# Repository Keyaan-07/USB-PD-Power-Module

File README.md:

# USB-PD-Power-Supply
Sometimes it happens that when playing with electronics, we need more than 5V or 9V. USB PD Power Supply Solves this issue.  
By using USB PD Protocol, it can negotiate more than 5V from the USB PD charger. It can give voltage outputs as supported by the PD charger from 5V to 20V and it also supports the new USB PPS protocol which allows us set the voltage according to our own needs. For Example, if some device needs 18V, PPS can do the task and it could supply voltage.  

USB PD Power Supply can use both PD and PPS to cupply voltage. The microcontroller is the OG RP2040, which communications with the AP33772SDKZ USB PD negotiator IC to negotiate voltage levels. The Voltage and max current settings are controllable using the two rotary encoders present on the PCB.  

## How the heck do you assemble this thing?
First of all, you start with the gerber and upload it to your desired pcb manufacturer, I am gonna use [PCB Power](https://pcbpower.com). Now you order the PCB and all the components, and you wait, after they arrive, you cook(assemble) the PCB. Then what you do is that you upload the code and start using, 3D printed case is optional but you could download the files for that too! Flash firmware(firmware to come in a few days) on RP2040 using thonny or other software and boom your [USB-PD-Power-supply](https://github.com/Keyaan-07/USB-PD-Power-Supply/) is ready

## Why I chose to make this Project
I chose to make this project mainly because of the power issues i face. A few days ago, I wanted to power a coil for an electromagnet, i was not able to power it because of power supply from the Power bank (5V) was not enough, so i had the idea of making this because my dad's phone has a USB PD Charger so i could use that charger to power electronics that require higher voltage. That type of a project would be too simple, so i also added two rotary encoders and make a dedicated power supply. 

# Images

<br>

<br>  

# BOM - Bill Of All Materials:

| ITEM NAME                                              | ITEM PRICE        | FUNCTION                                                       | URL                                                                                                                                                                                                                                                                                                                                                                                           |
| ------------------------------------------------------ | ----------------- | -------------------------------------------------------------- | --------------------------------------------------------------------------------------------------------------------------------------------------------------------------------------------------------------------------------------------------------------------------------------------------------------------------------------------------------------------------------------------- |
| PCB Manufacturing(5 units)                             | $29.20            | Main PCB                                                       | [https://pcbpower.com](https://pcbpower.com/)                                                                                                                                                                                                                                                                                                                                                 |
| PCB Components                                         | $32.12            | All the PCB Components                                         | [https://lcsc.com](https://lcsc.com/)                                                                                                                                                                                                                                                                                                                                                         |
| PCB Stencil                                            | $27.25            | Stencil for Assembly of PCB                                    | [https://pcbpower.com](https://pcbpower.com/)                                                                                                                                                                                                                                                                                                                                                 |
| OLED and Headers + M3 screws and inserts, Solder Paste | $9.13             | Displays voltage and current levels, assembly body, and solder | https://roboticsdna.in/product/1-3-inch-iic-128x64-oled-display-module-4-pin-blue/ ,  https://roboticsdna.in/product/m3-x-6mm-brass-heat-set-threaded-round-insert-nut-25-pcs/ ,  https://roboticsdna.in/product/m3-6mm-ss-25-pieces/ ,  https://roboticsdna.in/product/2-54mm-1x20-right-angle-female-header-strip-2/ ,   https://roboticsdna.in/product/original-mechanic-30g-solder-paste/ |
| 3d parts                                               | $7.98             | 3d parts                                                       | [https://3ding.in/](https://3ding.in/)                                                                                                                                                                                                                                                                                                                                                        |
| Total                                                  | $105.68           |                                                                |                                                                                                                                                                                                                                                                                                                                                                                               |
### Note: There are a few resistors and capacitors, which had very high minimum order quantity(MOQ), about 100 pieces so i had to forcefully include those, which i will be utilising in my next highway projects. And tbh the prices were very less(about $0.002 per piece) so i think it is alright

# PCB Components Breakdown:  

| Id | Designator                           | MPN                  | Footprint                                      | DNP | MOQ | Price  | Quantity | Designation                        | Amount | LCSC Part No. | Supplier and ref                                                                                                                           |
| -- | ------------------------------------ | -------------------- | ---------------------------------------------- | --- | --- | ------ | -------- | ---------------------------------- | ------ | ------------- | ------------------------------------------------------------------------------------------------------------------------------------------ |
| 1  | Q1,Q2                                | BSS138               | SOT-23                                         | No  | Yes | 0.0571 | 10       | BSS138                             | 0.571  | C82045        | https://www.lcsc.com/product-detail/MOSFETs_onsemi-BSS138LT1G_C82045.html?s_z=n_bss138                                                     |
| 2  | C21,C1,C2,C22                        | GRM21BR61H106KE43L   | C_0805_2012Metric                              | No  | Yes | 0.0509 | 100      | 10u                                | 5.09   | C440198       | https://www.lcsc.com/product-detail/Multilayer-Ceramic-Capacitors-MLCC-SMD-SMT_Samsung-Electro-Mechanics-CL21A106KBYQNNE_C2932476.html     |
| 3  | R17,R10,R9,R20,R18,R19,R7,R6,R8,R11  | RC0402FR-7W5K1L      | R_0402_1005Metric                              | No  | Yes | 0.0057 | 100      | 5.1k                               | 0.57   | C278598       | https://www.lcsc.com/product-detail/Chip-Resistor-Surface-Mount_PANASONIC-ERJ2RKF5101X_C278598.html                                        |
| 4  | C14,C15                              | GJM1555C1H150FB01D   | C_0402_1005Metric                              | No  | Yes | 0.021  | 20       | 15p                                | 0.42   | C441742       | https://www.lcsc.com/product-detail/Multilayer-Ceramic-Capacitors-MLCC-SMD-SMT_Murata-Electronics-GJM1555C1H150FB01D_C441742.html          |
| 5  | J5                                   | generic              | PinHeader_1x04_P2.54mm_Vertical                | Yes | Yes | 0      | 1        | Conn_01x04_Socket_external         | 0      |               | \-                                                                                                                                         |
| 6  | R2,R1,R5,R16                         | ERJPA2F1001X         | R_0402_1005Metric                              | No  | Yes | 0.027  | 20       | 1k                                 | 0.54   | C427241       | https://www.lcsc.com/product-detail/Chip-Resistor-Surface-Mount_PANASONIC-ERJPA2F1001X_C427241.html                                        |
| 7  | Q4,Q3                                | AON7672E             | TRANS_AONR21307                                | No  | No  | 0.7665 | 5        | AON7672E                           | 3.8325 | C176755       | https://www.lcsc.com/product-detail/MOSFETs_Alpha-Omega-Semicon-AON7262E_C176755.html                                                      |
| 8  | C12,C18,C4,C8,C13,C3,C7,C9,C6,C5,C17 | GRM155R61H104JE14D   | C_0402_1005Metric                              | No  | Yes | 0.0074 | 100      | 100n                               | 0.74   | C426067       | https://www.lcsc.com/product-detail/Multilayer-Ceramic-Capacitors-MLCC-SMD-SMT_Murata-Electronics-GRM155R61H104JE14D_C426067.html          |
| 9  | J1                                   | TYPE-C16PIN          | USB_C_Receptacle_XKB_U262-16XN-4BVC11          | No  | Yes | 0.0656 | 10       | USB_C_Receptacle_USB2.0_14P_RP2040 | 0.656  | C393939       | https://www.lcsc.com/product-detail/USB-Connectors_SHOU-HAN-TYPE-C16PIN_C393939.html?s_z=n_USB_C_Receptacle_XKB_U262-16XN-4BVC11           |
| 10 | C10,C11,C16                          | GRM155R61H105KE05D   | C_0402_1005Metric                              | No  | Yes | 0.0247 | 20       | 1u                                 | 0.494  | C1518208      | https://www.lcsc.com/product-detail/Multilayer-Ceramic-Capacitors-MLCC-SMD-SMT_Murata-Electronics-GRM155R61H105KE05D_C1518208.html         |
| 11 | J4                                   | generic              | PinHeader_1x03_P2.54mm_Vertical                | Yes | Yes | 0      | 1        | Conn_01x03_Pin_SWD                 | 0      |               | \-                                                                                                                                         |
| 12 | R13                                  | RCS040210K0FKED      | R_0402_1005Metric                              | No  | Yes | 0.0278 | 50       | 10k                                | 1.39   | C3020235      | https://www.lcsc.com/product-detail/Chip-Resistor-Surface-Mount_Vishay-Intertech-RCS040210K0FKED_C3020235.html                             |
| 13 | D1,D2                                | 16-213/GHC-YR1S1N/3T | LED_0402_1005Metric                            | No  | Yes | 0.0526 | 20       | LED                                | 1.052  | C2980183      | https://www.lcsc.com/product-detail/LED-Indication-Discrete_Everlight-Elec-16-213-GHC-YR1S1N-3T_C2980183.html?s_z=n_LED                    |
| 14 | U1                                   | RP2040               | QFN-56-1EP_7x7mm_P0.4mm_EP3.2x3.2mm            | No  | No  | 1.1274 | 2        | RP2040                             | 2.2548 | C2040         | https://www.lcsc.com/product-detail/Microcontrollers-MCU-MPU-SOC_Raspberry-Pi-RP2040_C2040.html?s_z=n_rp2040                               |
| 15 | J2                                   | TYPE-C16PIN          | USB_C_Receptacle_XKB_U262-16XN-4BVC11          | No  | No  | 0.0656 | 0        | USB_C_Receptacle_USB2.0_14P        | 0      | C393939       | https://www.lcsc.com/product-detail/USB-Connectors_SHOU-HAN-TYPE-C16PIN_C393939.html?s_z=n_USB_C_Receptacle_XKB_U262-16XN-4BVC11           |
| 16 | Y1                                   | ABM8-272-T3          | Crystal_SMD_3225-4Pin_3.2x2.5mm                | No  | No  | 0.3856 | 2        | Crystal_GND24                      | 0.7712 | C20625731     | https://www.lcsc.com/product-detail/Crystals_Abracon-LLC-ABM8-272-T3_C20625731.html?s_z=n_abm8                                             |
| 17 | D3,D4                                | ESDS314DBVR          | SOT-23-5                                       | No  | Yes | 0.2348 | 5        | ESDS314DBVR                        | 1.174  | C1847859      | https://www.lcsc.com/product-detail/ESD-and-Surge-Protection-TVS-ESD_Texas-Instruments-ESDS314DBVR_C1847859.html?s_z=n_ESDS314DBVR         |
| 18 | TH1                                  | NCP15XH103F03RC      | R_0402_1005Metric                              | No  | Yes | 0.0104 | 1        | 10k @ 25C                          | 0.0104 | C209959       | https://www.lcsc.com/product-detail/NTC-Thermistors_TDK-NTCG103JF103FT1_C209959.html                                                       |
| 19 | D5                                   | 16-213/GHC-YR1S1N/3T | LED_0402_1005Metric_Pad0.77x0.64mm_HandSolder  | No  | Yes | 0.0526 | 0        | LED                                | 0      | C2980183      | https://www.lcsc.com/product-detail/LED-Indication-Discrete_Everlight-Elec-16-213-GHC-YR1S1N-3T_C2980183.html?s_z=n_LED                    |
| 20 | R14                                  | ERJPA2J100X          | R_0402_1005Metric                              | No  | Yes | 0.0201 | 20       | 10                                 | 0.402  | C427198       | https://www.lcsc.com/product-detail/Chip-Resistor-Surface-Mount_PANASONIC-ERJPA2J100X_C427198.html                                         |
| 21 | J6                                   | 6.94108E+11          | BarrelJack_Wuerth_6941xx301002                 | Yes | Yes | 0      | 0        | Barrel_Jack                        | 0      |               |                                                                                                                                            |
| 22 | SW3                                  | EC11E1820402         | RotaryEncoder_Alps_EC11E-Switch_Vertical_H20mm | No  | Yes | 1.548  | 1        | RotaryEncoder_Switch_Current       | 1.548  | C361167       | https://www.lcsc.com/product-detail/Rotary-Encoders_ALPSALPINE-EC11E1820402_C361167.html                                                   |
| 23 | R4,R3                                | ERJ2GEJ270X          | R_0402_1005Metric                              | No  | Yes | 0.0039 | 100      | 27                                 | 0.39   | C278580       | https://www.lcsc.com/product-detail/Chip-Resistor-Surface-Mount_PANASONIC-ERJ2GEJ270X_C278580.html                                         |
| 24 | IC1                                  | AP33772DKZ-13        | AP33772SDKZ13FA01                              | No  | No  | 1.6472 | 2        | AP33772SDKZ-13-FA01                | 3.2944 | C5244513      | https://www.lcsc.com/product-detail/AC-DC-Controllers-and-Regulators_Diodes-Incorporated-AP33772DKZ-13_C5244513.html?s_z=n_AP3377          |
| 25 | SW2                                  | EC11E1820402         | RotaryEncoder_Alps_EC11E-Switch_Vertical_H20mm | No  | Yes | 1.548  | 1        | RotaryEncoder_Switch_Voltage       | 1.548  | C361167       | https://www.lcsc.com/product-detail/Rotary-Encoders_ALPSALPINE-EC11E1820402_C361167.html                                                   |
| 26 | U3                                   | W25Q128JVSIM         | SOIC-8_5.23x5.23mm_P1.27mm                     | No  | Yes | 1.1083 | 5        | W25Q128JVS                         | 5.5415 | C2613930      | https://www.lcsc.com/product-detail/NOR-FLASH_Winbond-Elec-W25Q128JVSIM_C2613930.html?s_z=n_W25Q128JVS                                     |
| 27 | R12                                  | PA0402FRL570R005L    | R_0402_1005Metric                              | No  | Yes | 0.0679 | 5        | 5m                                 | 0.3395 | C723468       | https://www.lcsc.com/product-detail/Current-Sense-Resistors-Shunt-Resistors_YAGEO-PA0402FRL570R005L_C723468.html                           |
| 28 | J3                                   | generic              | PinHeader_1x04_P2.54mm_Vertical                | Yes | Yes | 0      | 0        | Conn_01x04_Socket_OLED             | 0      |               |                                                                                                                                            |
| 29 | U2                                   | AMS1117S-3.3         | SOT-89-3                                       | No  | Yes | 0.1057 | 5        | AMS1117s-3.3                       | 0.5285 | C917152       | https://www.lcsc.com/product-detail/Voltage-Regulators-Linear-Low-Drop-Out-LDO-Regulators_JSMSEMI-AMS1117S-3-3_C917152.html?s_z=n_ams1117s |
| 30 | R15                                  | ERJPA2J101X          | R_0402_1005Metric                              | No  | Yes | 0.0374 | 20       | 100                                | 0.748  | C427204       | https://www.lcsc.com/product-detail/Chip-Resistor-Surface-Mount_PANASONIC-ERJPA2J101X_C427204.html                                         |
| 31 | SW1                                  | PTS810SJK250SMTRLFS  | SW_SPST_PTS810                                 | No  | No  | 0.6744 | 2        | SW_Push                            | 1.3488 | C221896       | https://www.lcsc.com/product-detail/Tactile-Switches_C-K-PTS810SJK250SMTRLFS_C221896.html?s_z=n_C221896                                    |

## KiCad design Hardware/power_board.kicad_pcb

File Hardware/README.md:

# Hardware for USB-PD-Power-supply is in this directory

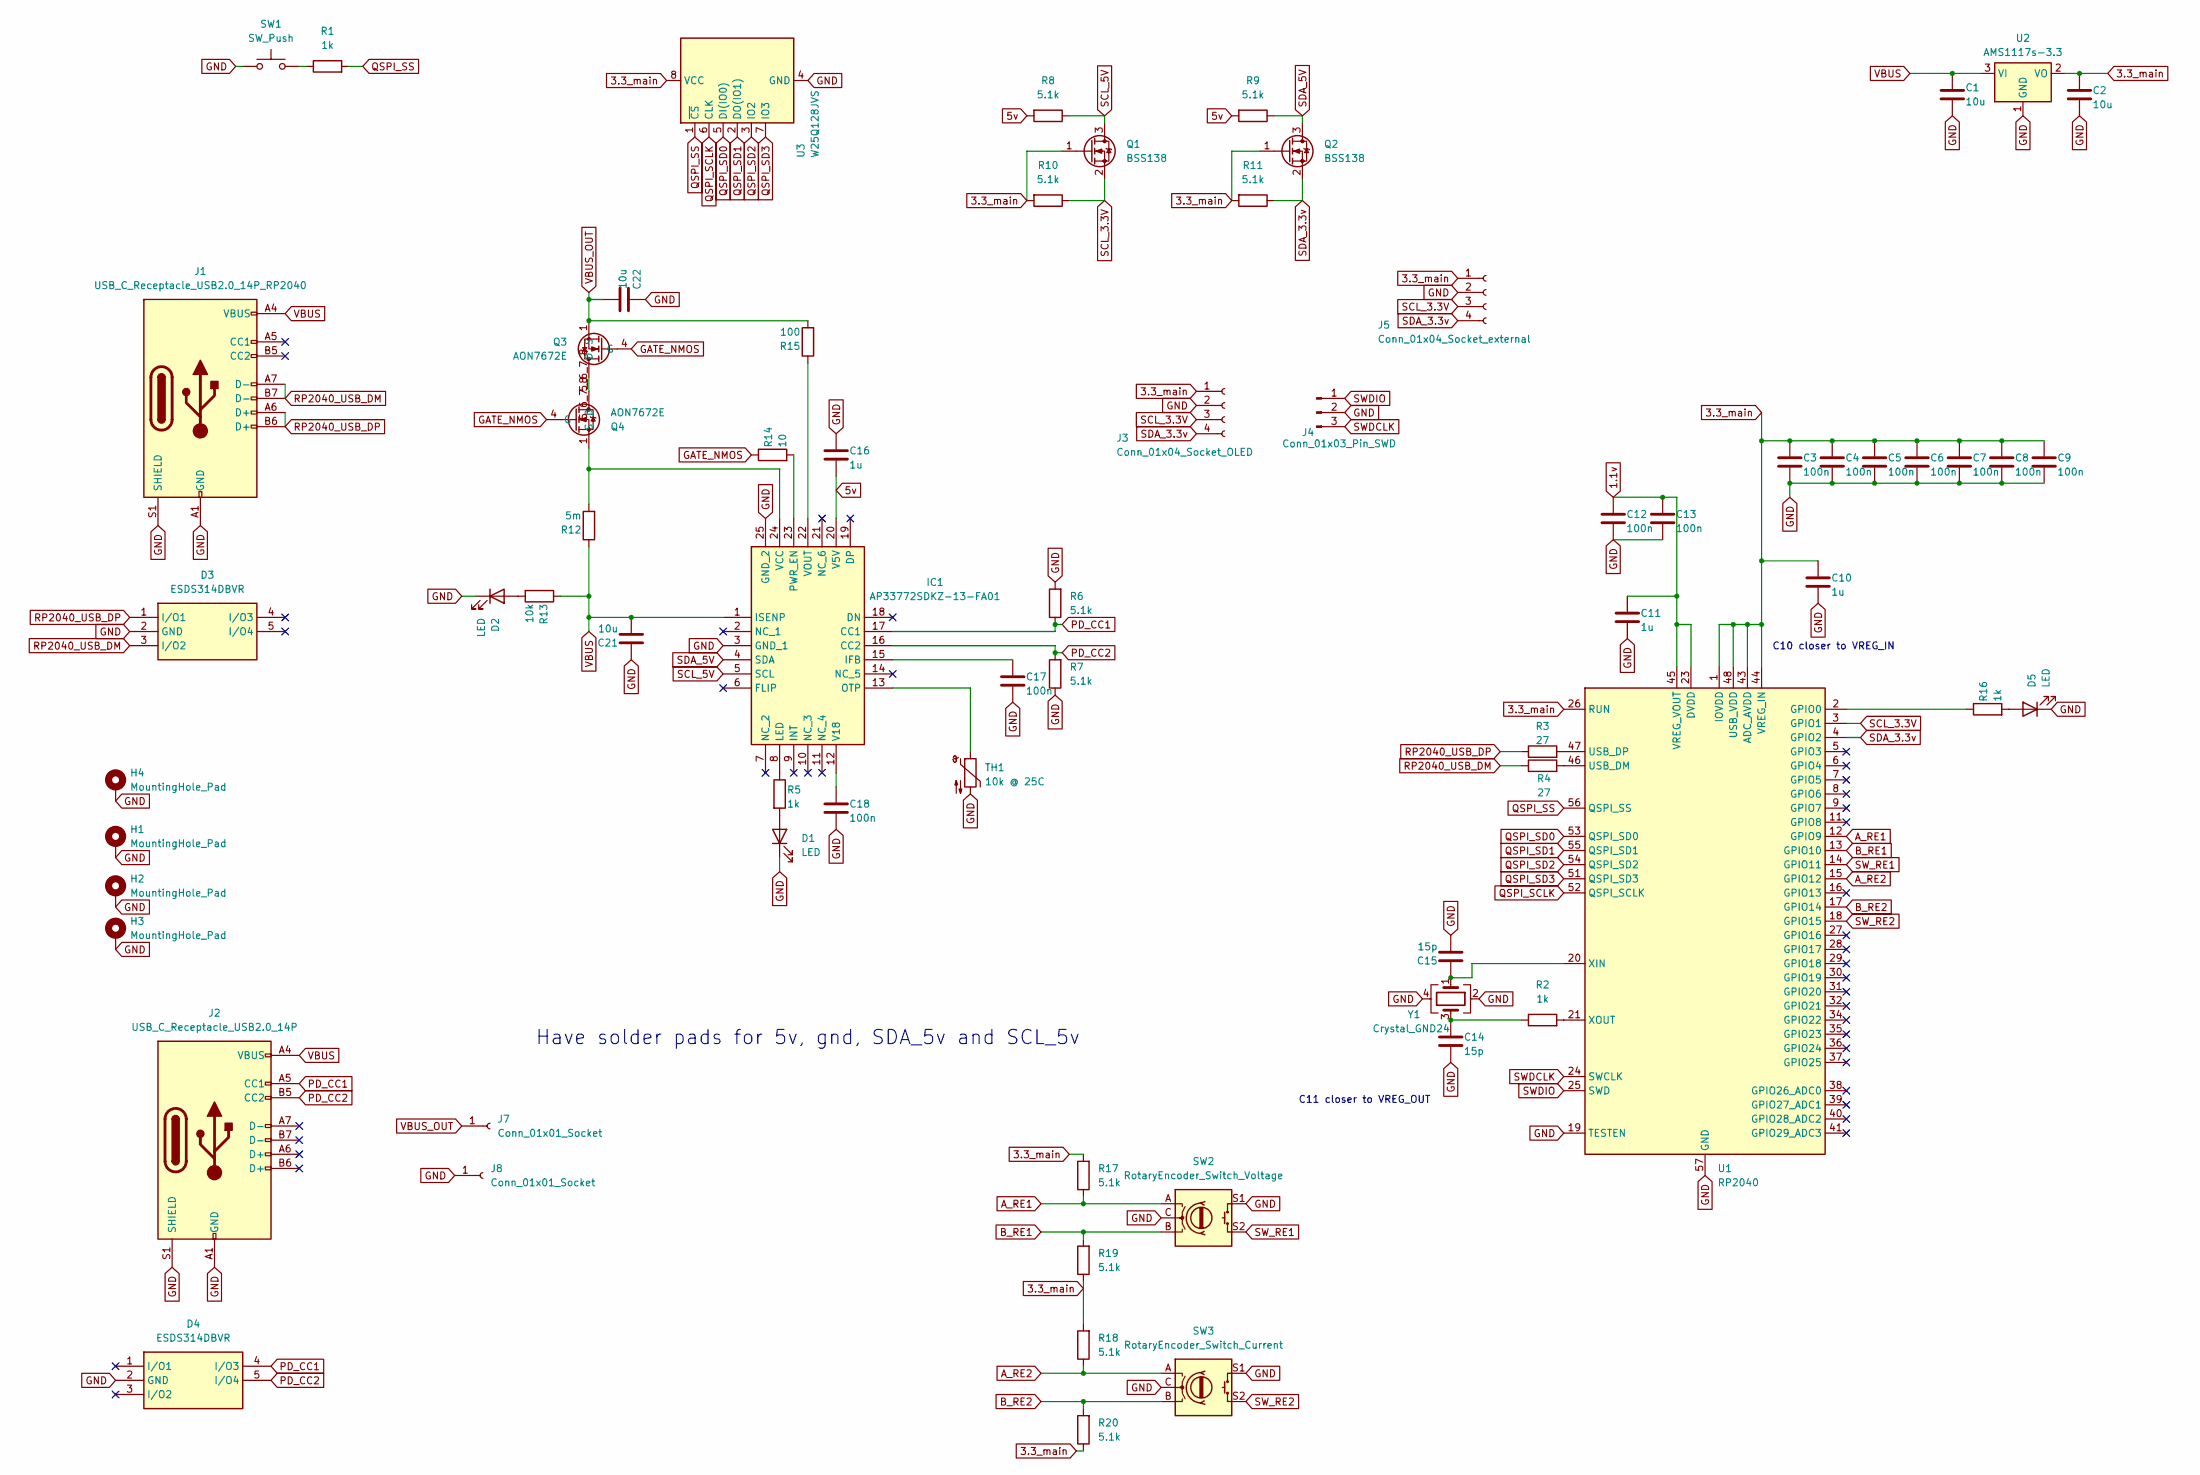
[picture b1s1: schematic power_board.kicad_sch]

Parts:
C1, C2, C21, C22: 10u; C_0805_2012Metric
C3, C4, C5, C6, C7, C8, C9, C12, C13, C17, C18: 100n; C_0402_1005Metric
C10, C11, C16: 1u; C_0402_1005Metric
C14, C15: 15p; C_0402_1005Metric
D1, D2: LED; LED_0402_1005Metric
D3, D4: ESDS314DBVR; SOT95P280X145-5N; Mouser Part Number 595-ESDS314DBVR
D5: LED; LED_0402_1005Metric_Pad0.77x0.64mm_HandSolder
H1, H2, H3, H4: MountingHole_Pad
IC1: AP33772SDKZ-13-FA01; AP33772SDKZ13FA01; Mouser Part Number 621-P33772SDKZ13FA01
J1: USB_C_Receptacle_USB2.0_14P_RP2040; USB_C_Receptacle_XKB_U262-16XN-4BVC11
J2: USB_C_Receptacle_USB2.0_14P; USB_C_Receptacle_XKB_U262-16XN-4BVC11
J3: Conn_01x04_Socket_OLED; PinHeader_1x04_P2.54mm_Vertical
J4: Conn_01x03_Pin_SWD; PinHeader_1x03_P2.54mm_Vertical
J5: Conn_01x04_Socket_external; PinHeader_1x04_P2.54mm_Vertical
J7, J8: Conn_01x01_Socket; Pin_D1.4mm_L8.5mm_W2.8mm_FlatFork
Q1, Q2: BSS138; SOT-23
Q3, Q4: AON7672E; TRANS_AONR21307
R1, R2, R5, R16: 1k; R_0402_1005Metric
R3, R4: 27; R_0402_1005Metric
R6, R7, R8, R9, R10, R11, R17, R18, R19, R20: 5.1k; R_0402_1005Metric
R12: 5m; R_0402_1005Metric
R13: 10k; R_0402_1005Metric
R14: 10; R_0402_1005Metric
R15: 100; R_0402_1005Metric
SW1: SW_Push; SW_SPST_PTS810
SW2: RotaryEncoder_Switch_Voltage; RotaryEncoder_Alps_EC11E-Switch_Vertical_H20mm
SW3: RotaryEncoder_Switch_Current; RotaryEncoder_Alps_EC11E-Switch_Vertical_H20mm
TH1: 10k @ 25C; R_0402_1005Metric
U1: RP2040; QFN-56-1EP_7x7mm_P0.4mm_EP3.2x3.2mm
U2: AMS1117s-3.3; SOT-89-3
U3: W25Q128JVS; SOIC-8_5.23x5.23mm_P1.27mm
Y1: Crystal_GND24; Crystal_SMD_3225-4Pin_3.2x2.5mm

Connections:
1.1v: C11.2, C12.2, C13.2, U1.23 (DVDD), U1.45 (VREG_VOUT), U1.50 (DVDD)
3.3_main: C2.2, C3.2, C4.2, C5.2, C6.2, C7.2, C8.2, C9.2, C10.2, J3.1, J5.1, Q1.1 (G), Q2.1 (G), R10.2, R11.2, R17.2, R18.2, R19.1, R20.1, U1.1 (IOVDD), U1.10 (IOVDD), U1.22 (IOVDD), U1.26 (RUN), U1.33 (IOVDD), U1.42 (IOVDD), U1.43 (ADC_AVDD), U1.44 (VREG_IN), U1.48 (USB_VDD), U1.49 (IOVDD), U2.2 (VO), U3.8 (VCC)
5v: C16.1, IC1.20 (V5V), R8.2, R9.2
A_RE1: R17.1, SW2.A, U1.12 (GPIO9)
A_RE2: R18.1, SW3.A, U1.15 (GPIO12)
B_RE1: R19.2, SW2.B, U1.13 (GPIO10)
B_RE2: R20.2, SW3.B, U1.17 (GPIO14)
GATE_NMOS: Q3.4 (G), Q4.4 (G), R14.1
GND: C1.1, C2.1, C3.1, C4.1, C5.1, C6.1, C7.1, C8.1, C9.1, C10.1, C11.1, C12.1, C13.1, C14.1, C15.1, C16.2, C17.1, C18.1, C21.2, C22.2, D1.1 (K), D2.1 (K), D3.2 (GND), D4.2 (GND), D5.1 (K), H1.1, H2.1, H3.1, H4.1, IC1.3 (GND_1), IC1.25 (GND_2), J1.A1 (GND), J1.A12 (GND), J1.B1 (GND), J1.B12 (GND), J1.S1 (SHIELD), J2.A1 (GND), J2.A12 (GND), J2.B1 (GND), J2.B12 (GND), J2.S1 (SHIELD), J3.2, J4.2, J5.2, J8.1, R6.2, R7.1, SW1.1, SW2.C, SW2.S1, SW3.C, SW3.S1, TH1.2, U1.19 (TESTEN), U1.57 (GND), U2.1 (GND), U3.4 (GND), Y1.2, Y1.4
unnamed: C14.2, R2.1, Y1.3
unnamed: D1.2 (A), R5.2
unnamed: D2.2 (A), R13.2
unnamed: D5.2 (A), R16.2
unnamed: C17.2, IC1.15 (IFB)
unnamed: IC1.8 (LED), R5.1
unnamed: IC1.13 (OTP), TH1.1
unnamed: IC1.23 (PWR_EN), R14.2
unnamed: C18.2, IC1.12 (V18)
unnamed: IC1.24 (VCC), Q4.1 (S), R12.2
unnamed: IC1.22 (VOUT), R15.1
unnamed: Q3.5_6_7_8 (D), Q4.5_6_7_8 (D)
unnamed: R1.1, SW1.2
unnamed: R16.1, U1.2 (GPIO0)
unnamed: R4.2, U1.46 (USB_DM)
unnamed: R3.2, U1.47 (USB_DP)
unnamed: C15.2, U1.20 (XIN), Y1.1
unnamed: R2.2, U1.21 (XOUT)
PD_CC1: D4.4 (I/O3), IC1.17 (CC1), J2.A5 (CC1), R6.1
PD_CC2: D4.5 (I/O4), IC1.16 (CC2), J2.B5 (CC2), R7.2
QSPI_SCLK: U1.52 (QSPI_SCLK), U3.6 (CLK)
QSPI_SD0: U1.53 (QSPI_SD0), U3.5 (DI(IO0))
QSPI_SD1: U1.55 (QSPI_SD1), U3.2 (DO(IO1))
QSPI_SD2: U1.54 (QSPI_SD2), U3.3 (IO2)
QSPI_SD3: U1.51 (QSPI_SD3), U3.7 (IO3)
QSPI_SS: R1.2, U1.56 (QSPI_SS), U3.1 (~CS)
RP2040_USB_DM: D3.3 (I/O2), J1.A7 (D-), J1.B7 (D-), R4.1
RP2040_USB_DP: D3.1 (I/O1), J1.A6 (D+), J1.B6 (D+), R3.1
SCL_3.3V: J3.3, J5.3, Q1.2 (S), R10.1, U1.3 (GPIO1)
SCL_5V: IC1.5 (SCL), Q1.3 (D), R8.1
SDA_3.3v: J3.4, J5.4, Q2.2 (S), R11.1, U1.4 (GPIO2)
SDA_5V: IC1.4 (SDA), Q2.3 (D), R9.1
SWDCLK: J4.3, U1.24 (SWCLK)
SWDIO: J4.1, U1.25 (SWD)
SW_RE1: SW2.S2, U1.14 (GPIO11)
SW_RE2: SW3.S2, U1.18 (GPIO15)
VBUS: C1.2, C21.1, IC1.1 (ISENP), J1.A4 (VBUS), J1.A9 (VBUS), J1.B4 (VBUS), J1.B9 (VBUS), J2.A4 (VBUS), J2.A9 (VBUS), J2.B4 (VBUS), J2.B9 (VBUS), R12.1, R13.1, U2.3 (VI)
VBUS_OUT: C22.1, J7.1, Q3.1 (S), R15.2

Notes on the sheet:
C10 closer to VREG_IN
Have solder pads for 5v, gnd, SDA_5v and SCL_5v
C11 closer to VREG_OUT

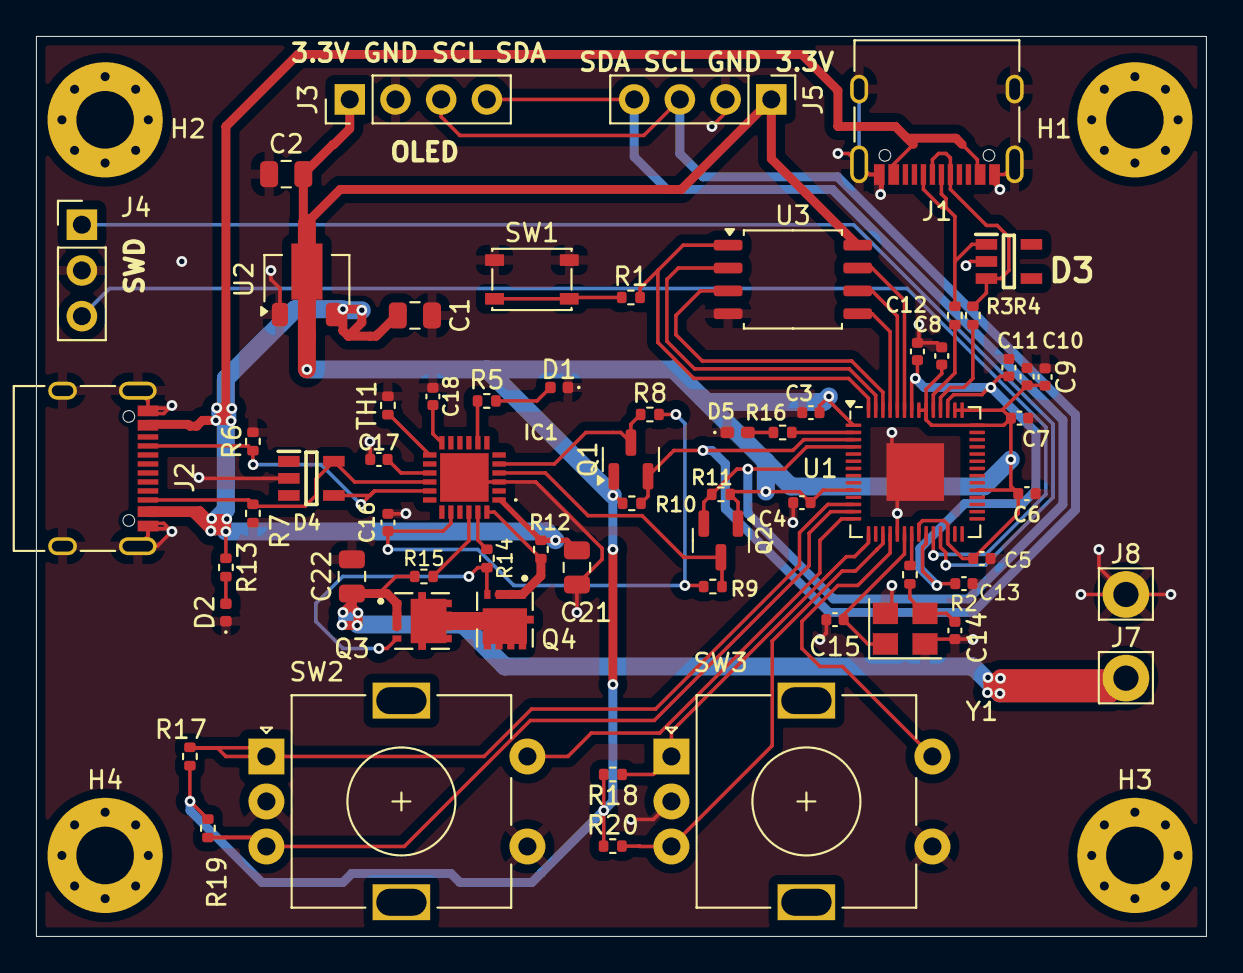
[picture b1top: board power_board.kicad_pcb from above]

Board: 2 copper layers, 65.0 x 50.0 mm, 69 parts (0 on the bottom side), 47 nets.

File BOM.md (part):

| Id | Designator                           | MPN                  | Footprint                                      | DNP | Price  | Quantity | Designation                        | Amount | Supplier and ref                                                                                                                           |
| -- | ------------------------------------ | -------------------- | ---------------------------------------------- | --- | ------ | -------- | ---------------------------------- | ------ | ------------------------------------------------------------------------------------------------------------------------------------------ |
| 1  | Q1,Q2                                | BSS138               | SOT-23                                         | No  | 0.0417 | 2        | BSS138                             | 0.0834 | https://www.lcsc.com/product-detail/MOSFETs_onsemi-BSS138LT1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                                                     |
| 2  | C21,C1,C2,C22                        | GRM21BR61H106KE43L   | C_0805_2012Metric                              | No  | 0.0703 | 4        | 10u                                | 0.2812 | https://www.lcsc.com/product-detail/Multilayer-Ceramic-Capac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          |
| 3  | R17,R10,R9,R20,R18,R19,R7,R6,R8,R11  | RC0402FR-7W5K1L      | R_0402_1005Metric                              | No  | 0.0019 | 10       | 5.1k                               | 0.019  | https://www.lcsc.com/product-detail/Chip-Resistor-Surface-Mo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                                        |
| 4  | C14,C15                              | GJM1555C1H150FB01D   | C_0402_1005Metric                              | No  | 0.021  | 2        | 15p                                | 0.042  | https://www.lcsc.com/product-detail/Multilayer-Ceramic-Capac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          |
| 5  | J5                                   | generic              | PinHeader_1x04_P2.54mm_Vertical                | Yes | 0      | 1        | Conn_01x04_Socket_external         | 0      | \-                                                                                                                                         |
| 6  | R2,R1,R5,R16                         | ERJPA2F1001X         | R_0402_1005Metric                              | No  | 0.0027 | 4        | 1k                                 | 0.0108 | https://www.lcsc.com/product-detail/Chip-Resistor-Surface-Mo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                                        |
| 7  | Q4,Q3                                | AON7672E             | TRANS_AONR21307                                | No  | 0.7665 | 2        | AON7672E                           | 1.533  | https://www.lcsc.com/product-detail/MOSFETs_Alpha-Omega-Semi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                                                      |
| 8  | C12,C18,C4,C8,C13,C3,C7,C9,C6,C5,C17 | GRM155R61H104JE14D   | C_0402_1005Metric                              | No  | 0.0074 | 11       | 100n                               | 0.0814 | https://www.lcsc.com/product-detail/Multilayer-Ceramic-Capac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          |
| 9  | J1                                   | TYPE-C16PIN          | USB_C_Receptacle_XKB_U262-16XN-4BVC11          | No  | 0.62   | 1        | USB_C_Receptacle_USB2.0_14P_RP2040 | 0.62   | https://www.lcsc.com/product-detail/USB-Connectors_SHOU-HAN-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           |
| 10 | C10,C11,C16                          | GRM155R61H105KE05D   | C_0402_1005Metric                              | No  | 0.0226 | 3        | 1u                                 | 0.0678 | https://www.lcsc.com/product-detail/Multilayer-Ceramic-Capac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         |
| 11 | J4                                   | generic              | PinHeader_1x03_P2.54mm_Vertical                | Yes | 0      | 1        | Conn_01x03_Pin_SWD                 | 0      | \-                                                                                                                                         |
| 12 | R13                                  | RCS040210K0FKED      | R_0402_1005Metric                              | No  | 0.0278 | 1        | 10k                                | 0.0278 | https://www.lcsc.com/product-detail/Chip-Resistor-Surface-Mo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                             |
| 13 | D1,D2                                | 16-213/GHC-YR1S1N/3T | LED_0402_1005Metric                            | No  | 0.0526 | 2        | LED                                | 0.1052 | https://www.lcsc.com/product-detail/LED-Indication-Discrete_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                    |
| 14 | U1                                   | RP2040               | QFN-56-1EP_7x7mm_P0.4mm_EP3.2x3.2mm            | No  | 1.1274 | 1        | RP2040                             | 1.1274 | https://www.lcsc.com/product-detail/Microcontrollers-MCU-MPU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                               |
| 15 | J2                                   | TYPE-C16PIN          | USB_C_Receptacle_XKB_U262-16XN-4BVC11          | No  | 0.62   | 1        | USB_C_Receptacle_USB2.0_14P        | 0.62   | https://www.lcsc.com/product-detail/USB-Connectors_SHOU-HAN-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           |
| 16 | Y1                                   | ABM8-272-T3          | Crystal_SMD_3225-4Pin_3.2x2.5mm                | No  | 0.3882 | 1        | Crystal_GND24                      | 0.3882 | https://www.lcsc.com/product-detail/Crystals_Abracon-LLC-ABM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                                             |
| 17 | D3,D4                                | ESDS314DBVR          | SOT95P280X145-5N                               | No  | 0.2314 | 2        | ESDS314DBVR                        | 0.4628 | https://www.lcsc.com/product-detail/ESD-and-Surge-Protection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         |
| 18 | TH1                                  | NCP15XH103F03RC      | R_0402_1005Metric                              | No  | 0.0104 | 1        | 10k @ 25C                          | 0.0104 | https://www.lcsc.com/product-detail/NTC-Thermistors_Murata-E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                            |
| 19 | D5                                   | 16-213/GHC-YR1S1N/3T | LED_0402_1005Metric_Pad0.77x0.64mm_HandSolder  | No  | 0.0526 | 1        | LED                                | 0.0526 | https://www.lcsc.com/product-detail/LED-Indication-Discrete_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                    |
| 20 | R14                                  | ERJPA2J100X          | R_0402_1005Metric                              | No  | 0.0201 | 1        | 10                                 | 0.0201 | https://www.lcsc.com/product-detail/Chip-Resistor-Surface-Mo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                                         |
| 21 | J6                                   | 6.94108E+11          | BarrelJack_Wuerth_6941xx301002                 | No  |        | 1        | Barrel_Jack                        | 0      |                                                                                                                                            |
| 22 | SW3                                  | EC11E1820402         | RotaryEncoder_Alps_EC11E-Switch_Vertical_H20mm | No  | 1.548  | 1        | RotaryEncoder_Switch_Current       | 1.548  | https://www.lcsc.com/product-detail/Rotary-Encoders_ALPSALPI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                                                   |
| 23 | R4,R3                                | ERJ2GEJ270X          | R_0402_1005Metric                              | No  | 0.0039 | 2        | 27                                 | 0.0078 | https://www.lcsc.com/product-detail/Chip-Resistor-Surface-Mo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                                         |
| 24 | IC1                                  | AP33772DKZ-13        | AP33772SDKZ13FA01                              | No  | 1.6472 | 1        | AP33772SDKZ-13-FA01                | 1.6472 | https://www.lcsc.com/product-detail/AC-DC-Controllers-and-Re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          |
| 25 | SW2                                  | EC11E1820402         | RotaryEncoder_Alps_EC11E-Switch_Vertical_H20mm | No  | 1.548  | 1        | RotaryEncoder_Switch_Voltage       | 1.548  | https://www.lcsc.com/product-detail/Rotary-Encoders_ALPSALPI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                                                   |
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
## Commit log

2025-05-29 Rename image.png to pcb.png
2025-05-29 Rename image.png to Bottom1
2025-05-29 Rename Bottom1 to Bottom1.png
